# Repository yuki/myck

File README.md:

# MyCK
MyCK (My Custom Keyboard) es un proyecto cuyo objetivo es aprender a crear un teclado customizado desde cero.

La idea surge tras ver teclados como:

- [Ergonaut One](https://github.com/ergonautkb/one)
- [Sweep](https://github.com/davidphilipbarr/Sweep)
- [crkbd](https://github.com/kluelesskk/crkbd)
- [Dilemma](https://github.com/Bastardkb/Dilemma)
- [Voyager](https://www.zsa.io/voyager)

Estos teclados usan el proyecto [QMK](https://qmk.fm/) para la creación del firmware que es instalado en un microcontrolador.

## Objetivos

La idea es entender y crear un teclado, y para ello los pasos a seguir van a ser:

- [x] Aprender los entresijos de un teclado a nivel electrónico.
- [ ] Aprender a usar [KiCad](https://www.kicad.org/)
  - [x] Crear esquema electrónico
  - [x] Crear PCB
  - [x] Mandarla crear?
- [x] Aprender a crear un custom firmware con [QMK](https://qmk.fm/)
  - [x] Hacer firmware básico para pruebas. Está en el directorio [qmk](./qmk)

## Imágenes

Esquema electrónico completo de cómo sería un teclado:

Esquema de la placa de pruebas:

Sólo las pistas para la placa de pruebas:

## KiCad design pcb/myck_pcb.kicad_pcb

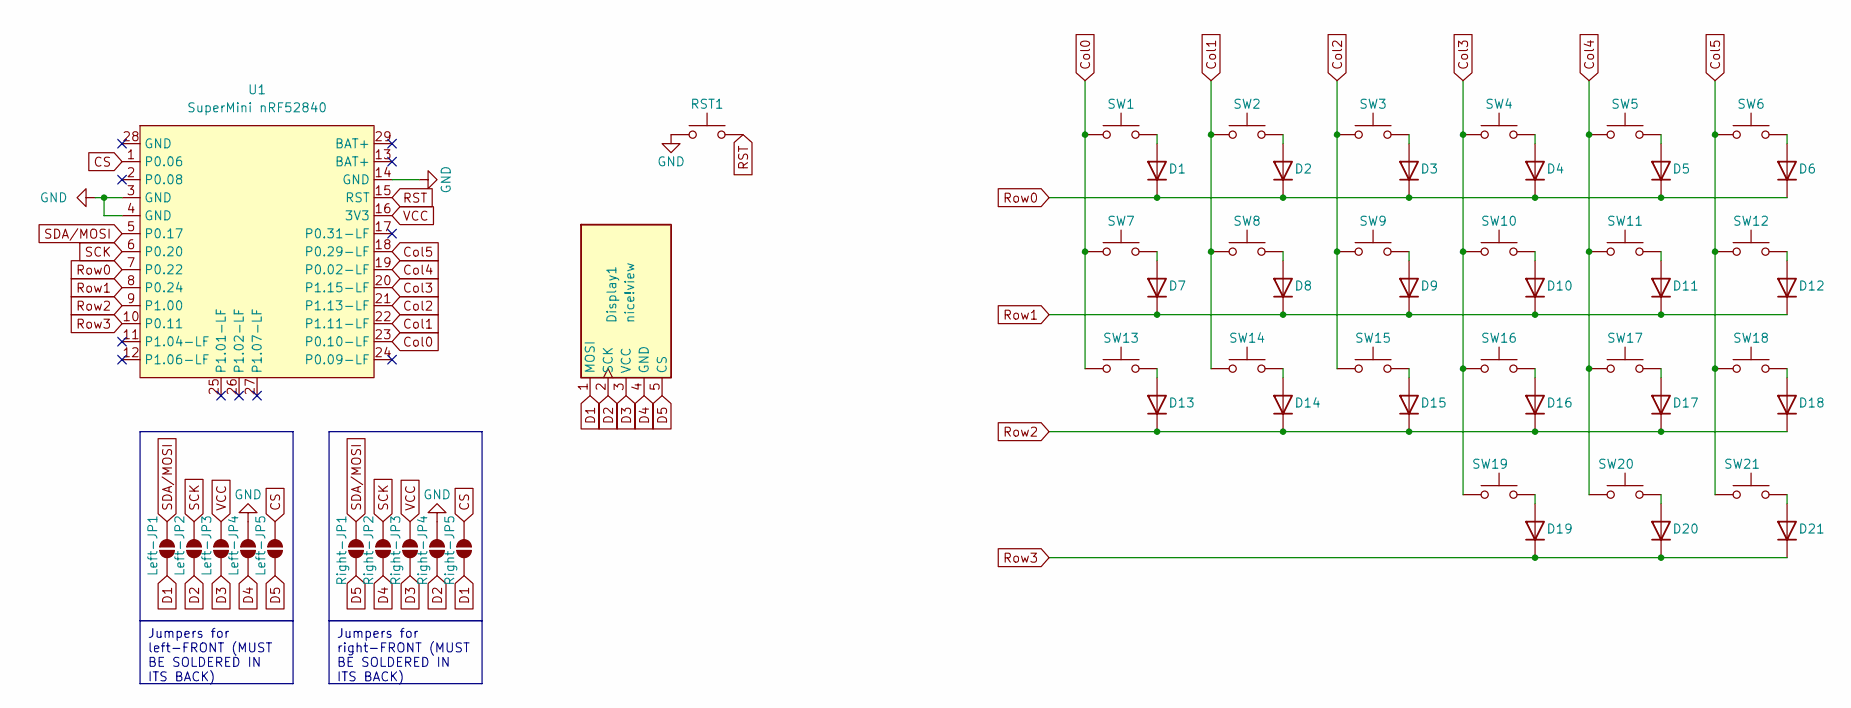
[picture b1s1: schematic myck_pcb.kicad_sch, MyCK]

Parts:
D1, D2, D3, D4, D5, D6, D7, D8, D9, D10, D11, D12, D13, D14, D15, D16, D17, D18, D19, D20, D21: D; Diode_TH_SMD_DUAL
Display1: nice!view; nice_view
Left-JP1, Left-JP2, Left-JP3, Left-JP4, Left-JP5: SolderJumper_2_Open; SolderJumper-2_P1.3mm_Open_TrianglePad1.0x1.5mm
RST1: SW_Push
Right-JP1, Right-JP2, Right-JP3, Right-JP4, Right-JP5: SolderJumper_2_Open; SolderJumper-2_P1.3mm_Open_TrianglePad1.0x1.5mm
SW1, SW2, SW3, SW4, SW5, SW6, SW7, SW8, SW9, SW10, SW11, SW12, SW13, SW14, SW15, SW16, SW17, SW18, SW19, SW20, SW21: SW_Push; KS-27_KS-33_Hotswap_1U_DUAL
U1: SuperMini nRF52840; SuperMini_nRF52840_AH_USBup

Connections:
CS: Left-JP5.2 (B), Right-JP5.2 (B), U1.1 (P0.06)
Col0: SW1.1, SW7.1, SW13.1, U1.23 (P0.10-LF)
Col1: SW2.1, SW8.1, SW14.1, U1.22 (P1.11-LF)
Col2: SW3.1, SW9.1, SW15.1, U1.21 (P1.13-LF)
Col3: SW4.1, SW10.1, SW16.1, SW19.1, U1.20 (P1.15-LF)
Col4: SW5.1, SW11.1, SW17.1, SW20.1, U1.19 (P0.02-LF)
Col5: SW6.1, SW12.1, SW18.1, SW21.1, U1.18 (P0.29-LF)
D1: Display1.1 (MOSI), Left-JP1.1 (A), Right-JP5.1 (A)
D2: Display1.2 (SCK), Left-JP2.1 (A), Right-JP4.1 (A)
D3: Display1.3 (VCC), Left-JP3.1 (A), Right-JP3.1 (A)
D4: Display1.4 (GND), Left-JP4.1 (A), Right-JP2.1 (A)
D5: Display1.5 (CS), Left-JP5.1 (A), Right-JP1.1 (A)
GND: Left-JP4.2 (B), RST1.1, Right-JP4.2 (B), U1.3 (GND), U1.4 (GND), U1.14 (GND)
unnamed: D1.2 (A), SW1.2
unnamed: D2.2 (A), SW2.2
unnamed: D3.2 (A), SW3.2
unnamed: D4.2 (A), SW4.2
unnamed: D5.2 (A), SW5.2
unnamed: D6.2 (A), SW6.2
unnamed: D7.2 (A), SW7.2
unnamed: D8.2 (A), SW8.2
unnamed: D9.2 (A), SW9.2
unnamed: D10.2 (A), SW10.2
unnamed: D11.2 (A), SW11.2
unnamed: D12.2 (A), SW12.2
unnamed: D13.2 (A), SW13.2
unnamed: D14.2 (A), SW14.2
unnamed: D15.2 (A), SW15.2
unnamed: D16.2 (A), SW16.2
unnamed: D17.2 (A), SW17.2
unnamed: D18.2 (A), SW18.2
unnamed: D19.2 (A), SW19.2
unnamed: D20.2 (A), SW20.2
unnamed: D21.2 (A), SW21.2
RST: RST1.2, U1.15 (RST)
Row0: D1.1 (K), D2.1 (K), D3.1 (K), D4.1 (K), D5.1 (K), D6.1 (K), U1.7 (P0.22)
Row1: D7.1 (K), D8.1 (K), D9.1 (K), D10.1 (K), D11.1 (K), D12.1 (K), U1.8 (P0.24)
Row2: D13.1 (K), D14.1 (K), D15.1 (K), D16.1 (K), D17.1 (K), D18.1 (K), U1.9 (P1.00)
Row3: D19.1 (K), D20.1 (K), D21.1 (K), U1.10 (P0.11)
SCK: Left-JP2.2 (B), Right-JP2.2 (B), U1.6 (P0.20)
SDA/MOSI: Left-JP1.2 (B), Right-JP1.2 (B), U1.5 (P0.17)
VCC: Left-JP3.2 (B), Right-JP3.2 (B), U1.16 (3V3)

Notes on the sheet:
Jumpers for left-FRONT (MUST BE SOLDERED IN ITS BACK)
Jumpers for right-FRONT (MUST BE SOLDERED IN ITS BACK)

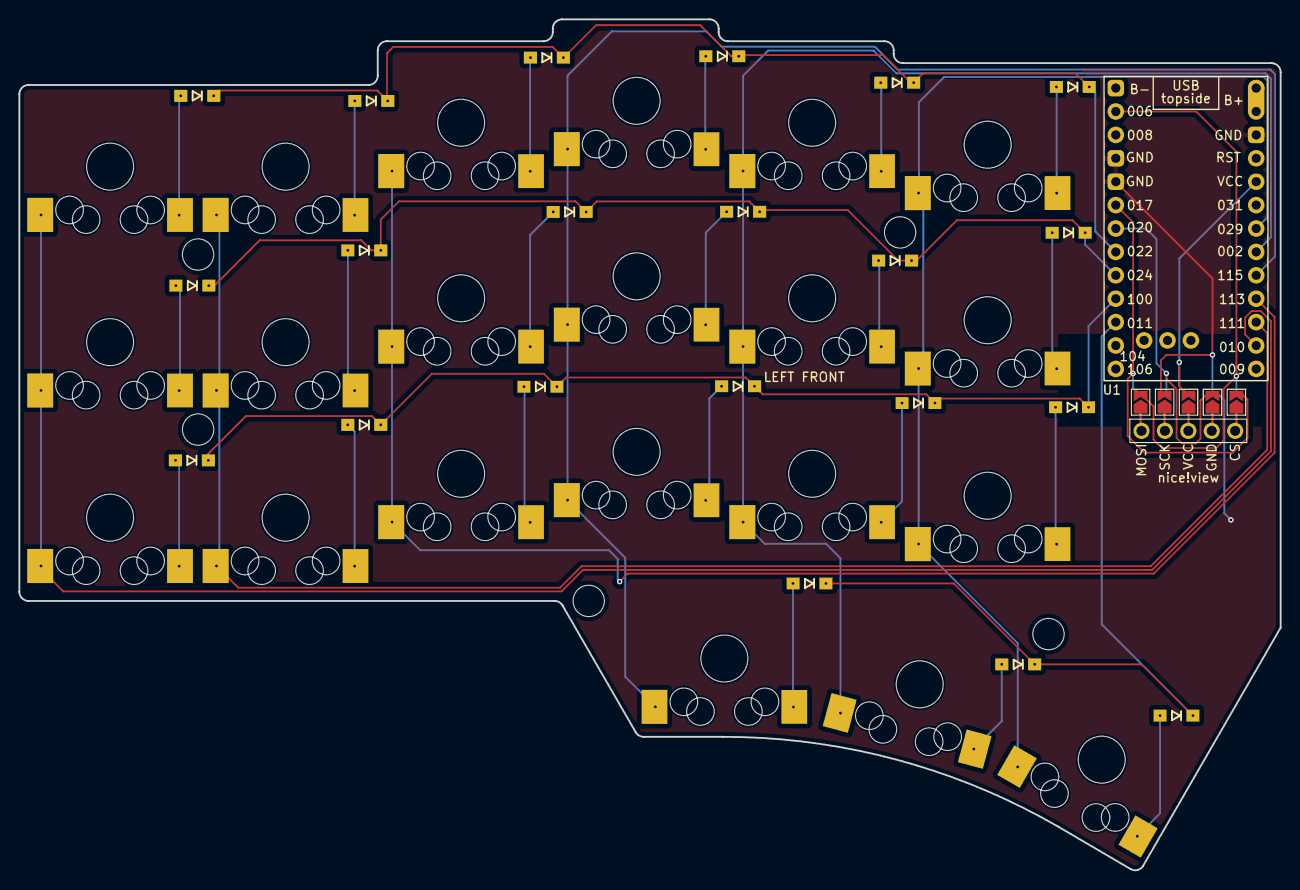
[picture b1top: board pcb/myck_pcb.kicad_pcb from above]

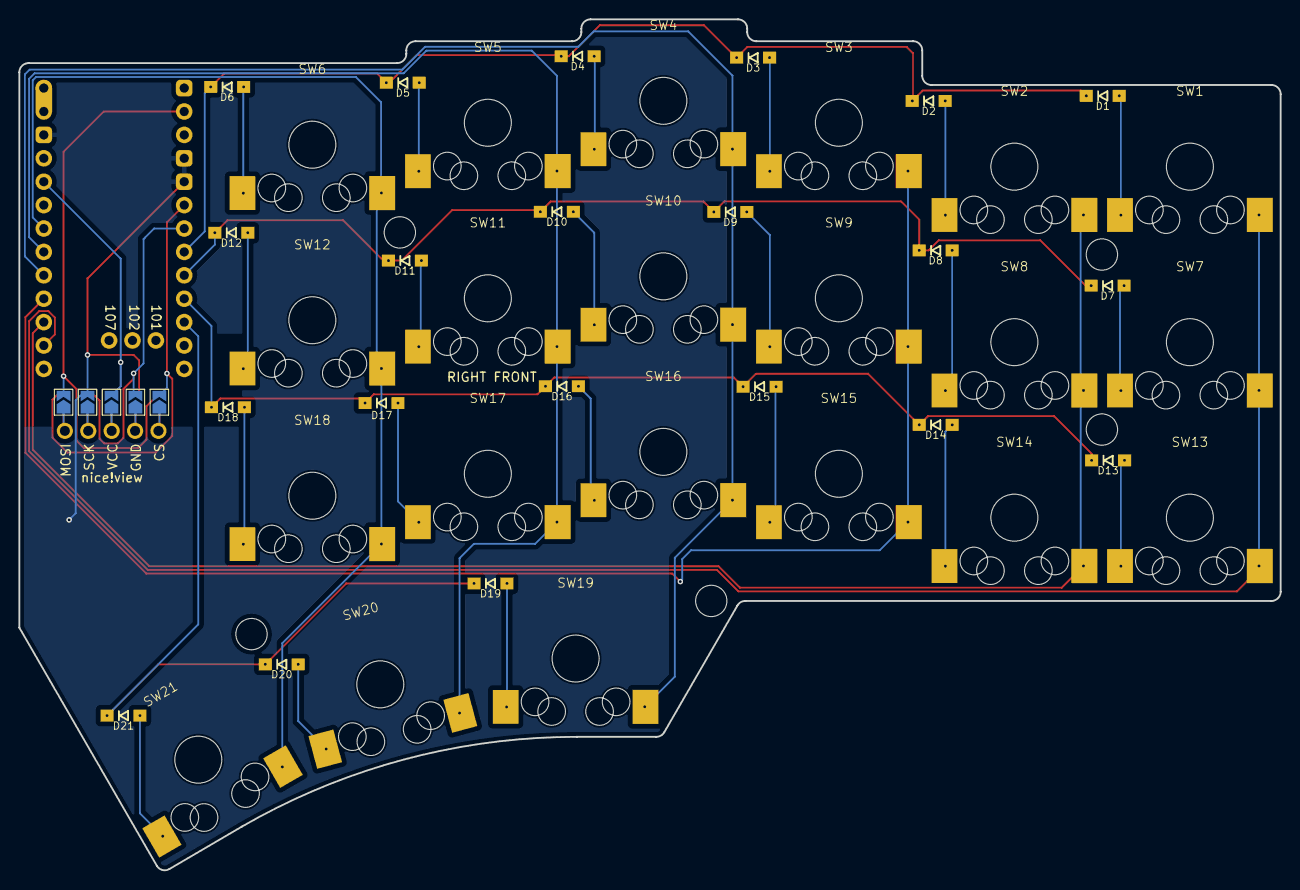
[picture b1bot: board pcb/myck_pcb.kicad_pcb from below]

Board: 2 copper layers, 136.9 x 92.4 mm, 54 parts (5 on the bottom side), 41 nets.

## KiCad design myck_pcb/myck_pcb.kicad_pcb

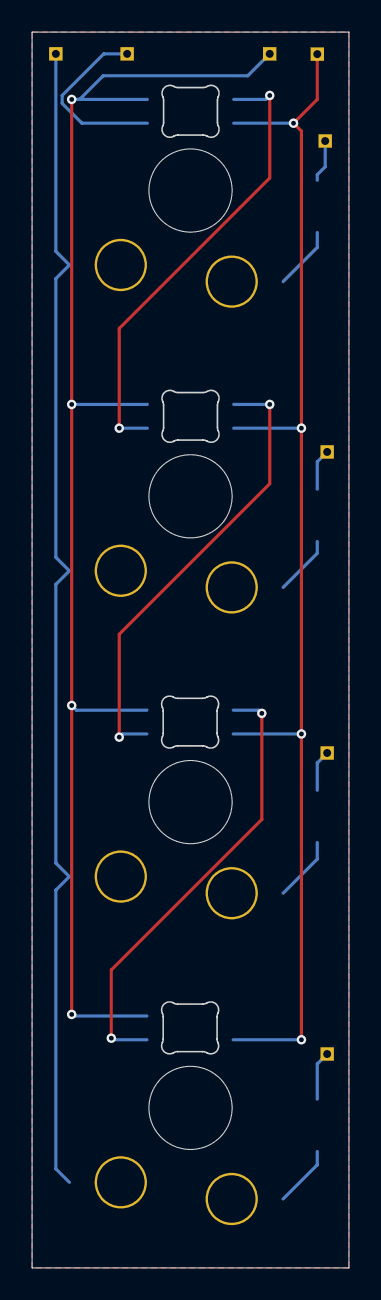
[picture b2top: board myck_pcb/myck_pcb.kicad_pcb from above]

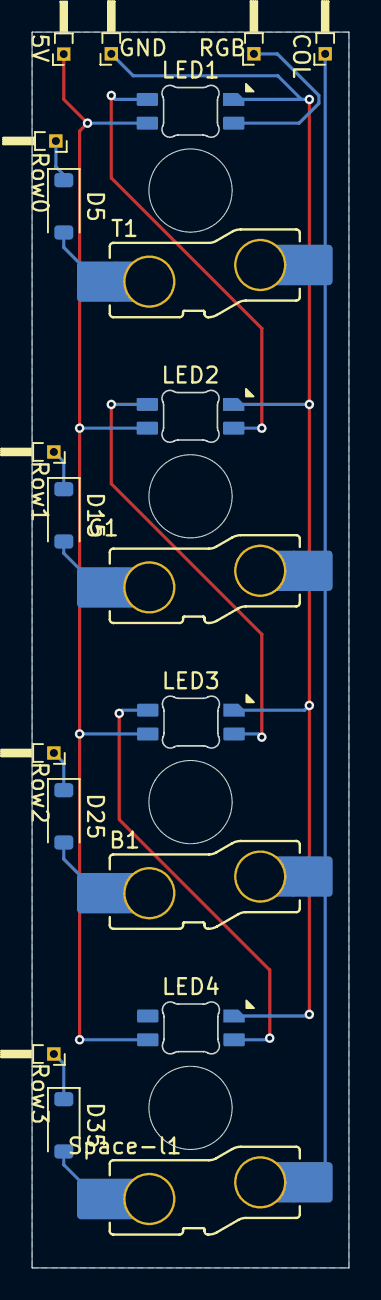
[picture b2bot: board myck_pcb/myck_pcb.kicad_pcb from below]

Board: 2 copper layers, 20.0 x 78.0 mm, 20 parts (20 on the bottom side), 11 nets.

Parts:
5V: PinHeader_1x01_P1.00mm_Horizontal
B1: SW_Push_45deg; SW_KS33_HS_KS-2P02B01-02_HS_1u
COL: PinHeader_1x01_P1.00mm_Horizontal
D5, D15, D25, D35: D; D_SOD-123
G1: SW_Push_45deg; SW_KS33_HS_KS-2P02B01-02_HS_1u
GND: PinHeader_1x01_P1.00mm_Horizontal
LED1, LED2, LED3, LED4: MX_SK6812MINI-E; LED_MX_6028R
RGB: PinHeader_1x01_P1.00mm_Horizontal
Row0, Row1, Row2, Row3: PinHeader_1x01_P1.00mm_Horizontal
Space-l1: SW_Push_45deg; SW_KS33_HS_KS-2P02B01-02_HS_1u
T1: SW_Push_45deg; SW_KS33_HS_KS-2P02B01-02_HS_1u

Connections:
+5V: 5V.1, LED1.1 (VDD), LED2.1 (VDD), LED3.1 (VDD), LED4.1 (VDD)
Col5: B1.1, COL.1, G1.1, Space-l1.1, T1.1
Earth: GND.1, LED1.4 (VSS), LED2.4 (VSS), LED3.4 (VSS), LED4.4 (VSS)
unnamed: D5.2 (A), T1.2
unnamed: D15.2 (A), G1.2
unnamed: B1.2, D25.2 (A)
unnamed: D35.2 (A), Space-l1.2
unnamed: LED1.2 (DOUT), LED2.3 (DIN)
unnamed: LED2.2 (DOUT), LED3.3 (DIN)
unnamed: LED3.2 (DOUT), LED4.3 (DIN)
RGB: LED1.3 (DIN), RGB.1

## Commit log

2024-12-05 Creado esquema electrónico básico
    Creado un esquema básico electrónico, con los switches más utilizados en
    un teclado normal.
2024-12-05 Cambiada imagen PNG a SVG
    Así mejor, y la imagen es escalable. No había visto la opción de
    exportar a SVG.
2025-01-12 Creado esquema PCB
    La PCB inicial, como es una prueba, sólo va a tener 4 teclas.
    Empezando a añadir RGB-leds
2025-01-13 Añadidos Leds, circuitos y pines
    En principio, creo que ya estaría la circuitería hecha.
2025-01-14 Movidos los footprints a directorio local
    Exportados los footprints utilizados (cogidos de varias librerías de
    internet) a directorio local. Así al abrir el proyecto en otro equipo,
    están todos los footprints necesarios.
2025-01-14 Versión 0.1-pruebas
    He hecho el pedido de esta versión sin nada soldado.
2025-01-20 Añadido firmware QMK de pruebas
    Testeado en la placa RP2040 con cables.
2025-01-26 Creado esquema electrónico
2025-01-29 Añadidos footprints propios y empezando la PCB
    Añadidos footprints propios para:
    - diodos
    - switches
    - microcontrolador
2025-01-31 Footprints modificados y posicionados en PCB
    Faltan los agujeros de la PCB. Todos los objetos lockeados, para evitar
    que se muevan.
2025-02-04 Añadidos nice!view reversible
    Añadida la opción de tener un nice!view en modo reversible (para ello
    se han añadido varios jumpers que tienen que ser soldados antes).
2025-02-04 Cableado de los diodos terminado
    Pequeña modificación en el tamaño de la placa para ignorar errores.
2025-02-04 Modificada la PCB
    Para que sea más parecida a un teclado normal.
    Dejado hueco para una batería más grande?
2025-02-05 Cambios en los jumpers del display
    Ahora los jumpers se tienen que soldar en la parte trasera de cada lado (tiene más sentido, todas las soldaduras en la parte de atrás de cada lado).
    Añadido una vía de GND para rellenar más zona.

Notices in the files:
myck_pcb/myck_pcb.kicad_sch:
License: MIT
